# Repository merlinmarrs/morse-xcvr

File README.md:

# morse-xcvr
A mini battery-powered morse radio network

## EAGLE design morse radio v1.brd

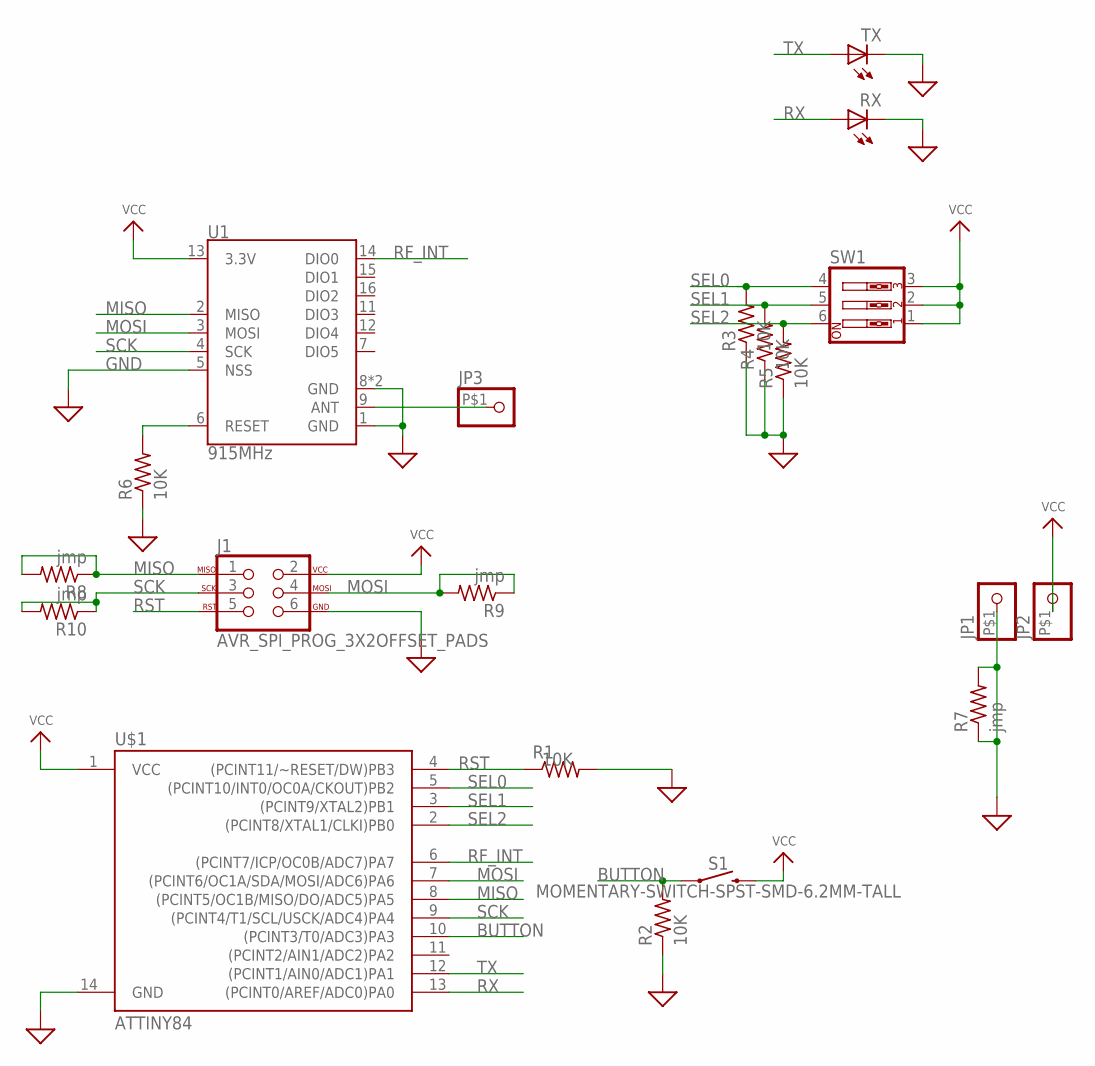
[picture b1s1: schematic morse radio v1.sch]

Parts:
J1: AVR_SPI_PROG_3X2OFFSET_PADS; 2X3_OFFSET
JP1, JP2, JP3: PINHD-1X1-BIGPOGO; 1X1-BIGPOGO
R1, R2, R3, R4, R5, R6: 10K; M1206
R7, R8, R9, R10: jmp; M1206
RX: LEDSMT1206; 1206
S1: MOMENTARY-SWITCH-SPST-SMD-6.2MM-TALL; TACTILE_SWITCH_SMD_6.2MM_TALL
SW1: SW_DIP-3; EDG-03
TX: LEDSMT1206; 1206
U1: 915MHz; RFM69HCW-XXXS2
U$1: ATTINY84; SO14

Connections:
BUTTON: R2.2, S1.A2 (1), U$1.10 ((PCINT3/T0/ADC3)PA3)
GND: J1.6, JP1.P$1, R1.2, R2.1, R3.1, R4.1, R5.1, R6.1, R7.1, R7.2, RX.C, TX.C, U1.1 (GND), U1.5 (NSS), U1.8 (GND), U1.10 (GND), U$1.14 (GND)
MISO: J1.1, R8.1, R8.2, U1.2 (MISO), U$1.8 ((PCINT5/OC1B/MISO/DO/ADC5)PA5)
MOSI: J1.4, R9.1, R9.2, U1.3 (MOSI), U$1.7 ((PCINT6/OC1A/SDA/MOSI/ADC6)PA6)
unnamed: JP3.P$1, U1.9 (ANT)
unnamed: R6.2, U1.6 (RESET)
RF_INT: U1.14 (DIO0), U$1.6 ((PCINT7/ICP/OC0B/ADC7)PA7)
RST: J1.5, R1.1, U$1.4 ((PCINT11/~RESET/DW)PB3)
RX: RX.A, U$1.13 ((PCINT0/AREF/ADC0)PA0)
SCK: J1.3, R10.1, R10.2, U1.4 (SCK), U$1.9 ((PCINT4/T1/SCL/USCK/ADC4)PA4)
SEL0: R3.2, SW1.4, U$1.5 ((PCINT10/INT0/OC0A/CKOUT)PB2)
SEL1: R4.2, SW1.5, U$1.3 ((PCINT9/XTAL2)PB1)
SEL2: R5.2, SW1.6, U$1.2 ((PCINT8/XTAL1/CLKI)PB0)
TX: TX.A, U$1.12 ((PCINT1/AIN0/ADC1)PA1)
VCC: J1.2, JP2.P$1, S1.B2 (2), SW1.1, SW1.2, SW1.3, U1.13 (3.3V), U$1.1 (VCC)

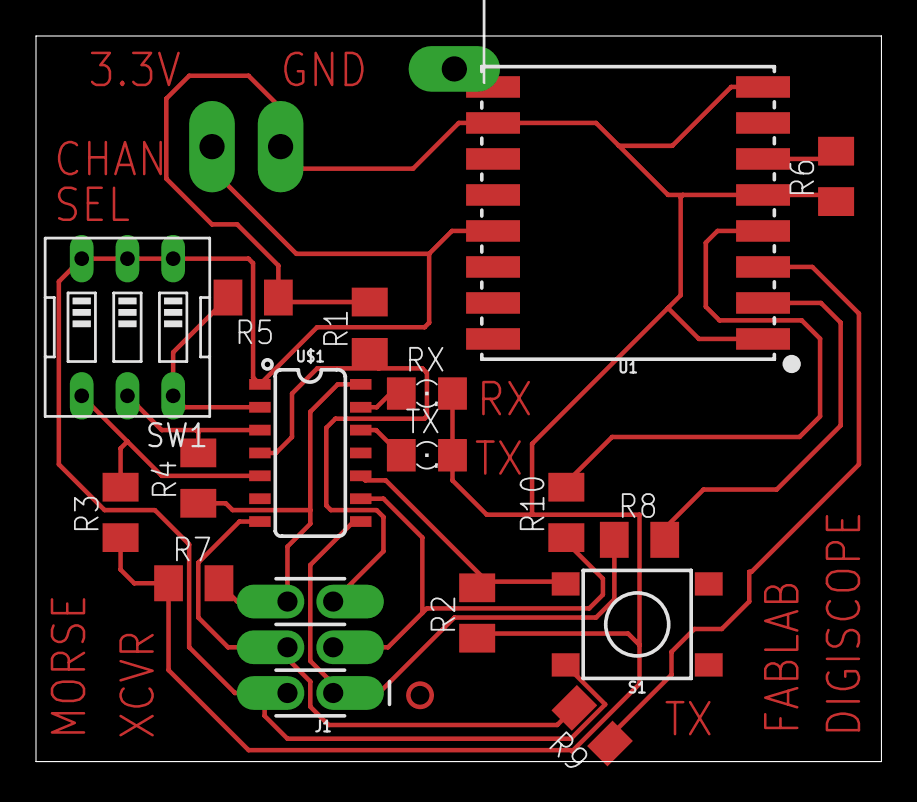
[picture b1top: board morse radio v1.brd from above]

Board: 2 copper layers, 47.0 x 40.3 mm, 20 parts (0 on the bottom side), 15 nets.

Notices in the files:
parts and their libraries:
SparkFun-Connectors: Licensing: Creative Commons ShareAlike 4.0 International - https://creativecommons.org/licenses/by-sa/4.0
